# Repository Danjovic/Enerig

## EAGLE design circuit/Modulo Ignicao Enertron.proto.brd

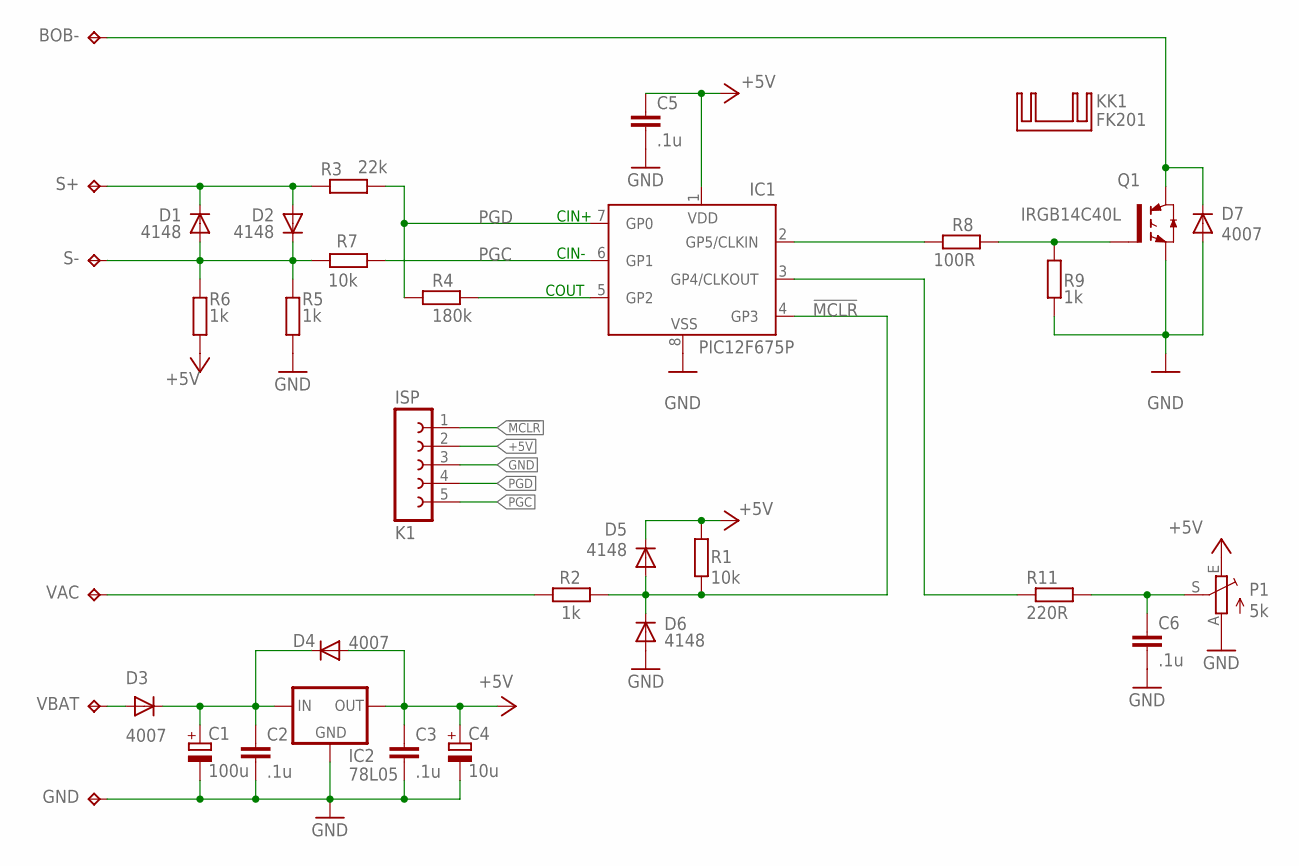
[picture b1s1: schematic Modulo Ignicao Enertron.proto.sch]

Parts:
BOB-: TPPAD1-13Y; P1-13Y
C1: 100u; E2,5-6
C2, C3, C5, C6: .1u; C050-025X075L
C4: 10u; E2-4
D1, D2, D5, D6: 4148; D-5L
D3, D4: 4007; D-7.5
D7: 4007; DO07
GND: TPPAD1-13Y; P1-13Y
IC1: PIC12F675P; DIL8
IC2: 78L05; TO92-
K1: ISP; FE05-1
KK1: FK201
P1: 5k; CA6V
Q1: IRGB14C40L; TO262-V
R1, R7: 10k; 0207/7L
R2, R5, R6, R9: 1k; 0207/7L
R3: 22k; 0207/7L
R4: 180k; 0207/7L
R8: 100R; 0207/7L
R11: 220R; 0207/7L
S+: TPPAD1-13Y; P1-13Y
S-: TPPAD1-13Y; P1-13Y
VAC: TPPAD1-13Y; P1-13Y
VBAT: TPPAD1-13Y; P1-13Y

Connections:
!MCLR: D5.A, D6.C, IC1.4 (GP3), K1.1, R1.3 (1), R2.3 (1)
+5V: C3.1, C4.+, C5.1, D4.A, D5.C, IC1.1 (VDD), IC2.3 (OUT), K1.2, P1.E, R1.4 (2), R6.3 (1)
COUT: IC1.5 (GP2), R4.4 (2)
GND: C1.-, C2.2, C3.2, C4.-, C5.2, C6.2, D6.A, D7.A, GND.TP, IC1.8 (VSS), IC2.2 (GND), K1.3, P1.A, Q1.3 (E), R5.3 (1), R9.3 (1)
unnamed: C1.+, C2.1, D3.C, D4.C, IC2.1 (IN)
unnamed: D1.A, D2.C, R5.4 (2), R6.4 (2), R7.4 (2), S-.TP
unnamed: IC1.2 (GP5/CLKIN), R8.3 (1)
unnamed: D1.C, D2.A, R3.3 (1), S+.TP
unnamed: Q1.1 (G), R8.4 (2), R9.4 (2)
unnamed: D3.A, VBAT.TP
unnamed: IC1.3 (GP4/CLKOUT), R11.3 (1)
unnamed: C6.1, P1.S, R11.4 (2)
unnamed: BOB-.TP, D7.C, Q1.2 (C)
unnamed: R2.4 (2), VAC.TP
PGC: IC1.6 (GP1), K1.5, R7.3 (1)
PGD: IC1.7 (GP0), K1.4, R3.4 (2), R4.3 (1)

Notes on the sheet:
CIN+
CIN-
COUT

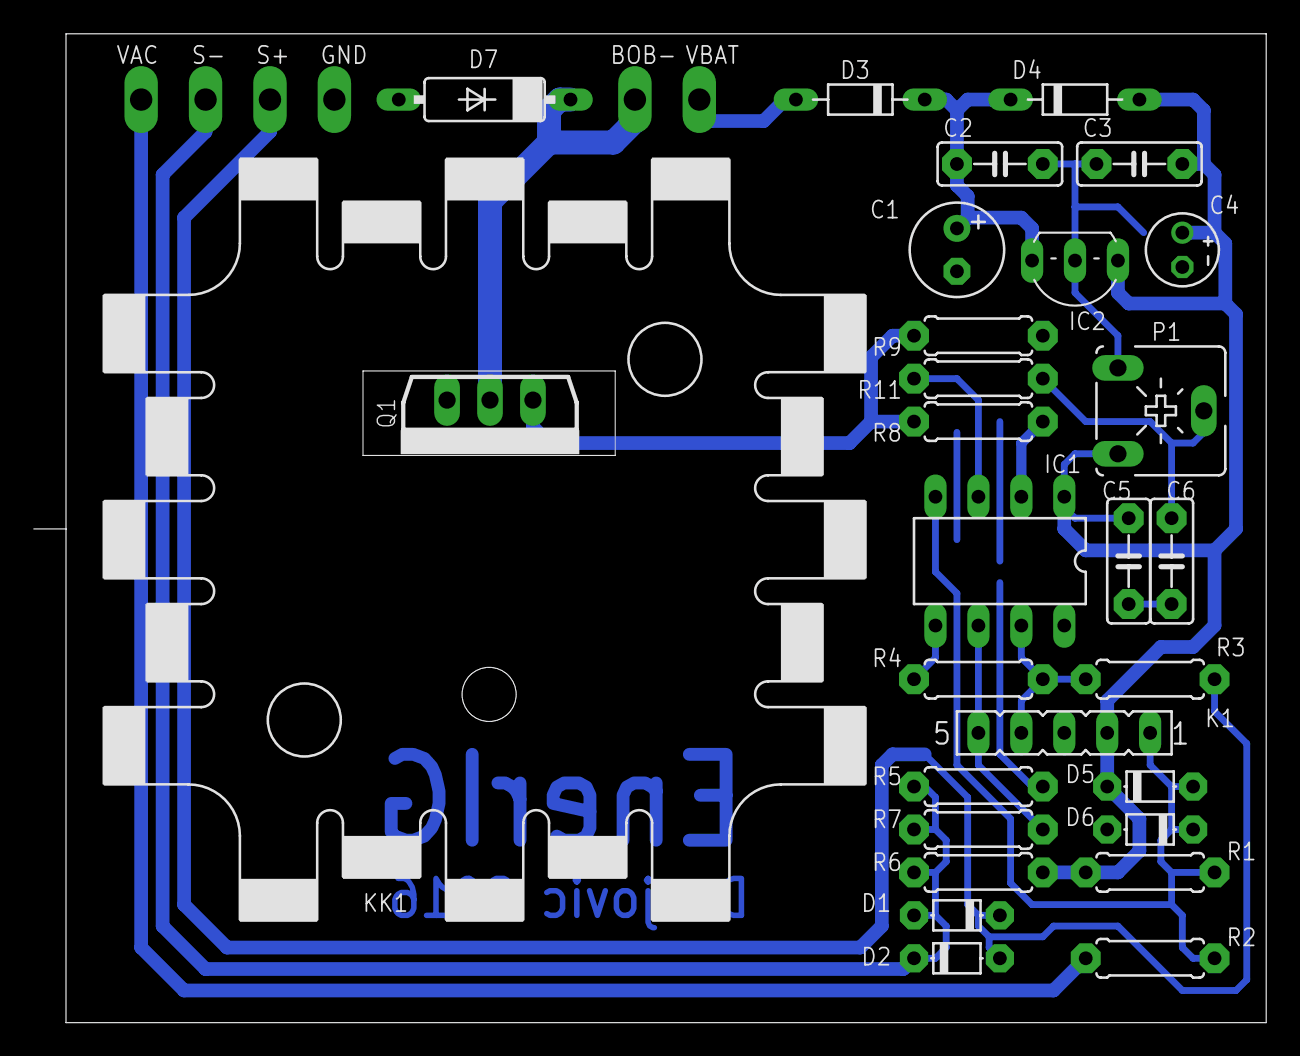
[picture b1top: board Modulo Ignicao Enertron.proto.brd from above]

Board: 2 copper layers, 72.9 x 58.5 mm, 35 parts (0 on the bottom side), 16 nets.

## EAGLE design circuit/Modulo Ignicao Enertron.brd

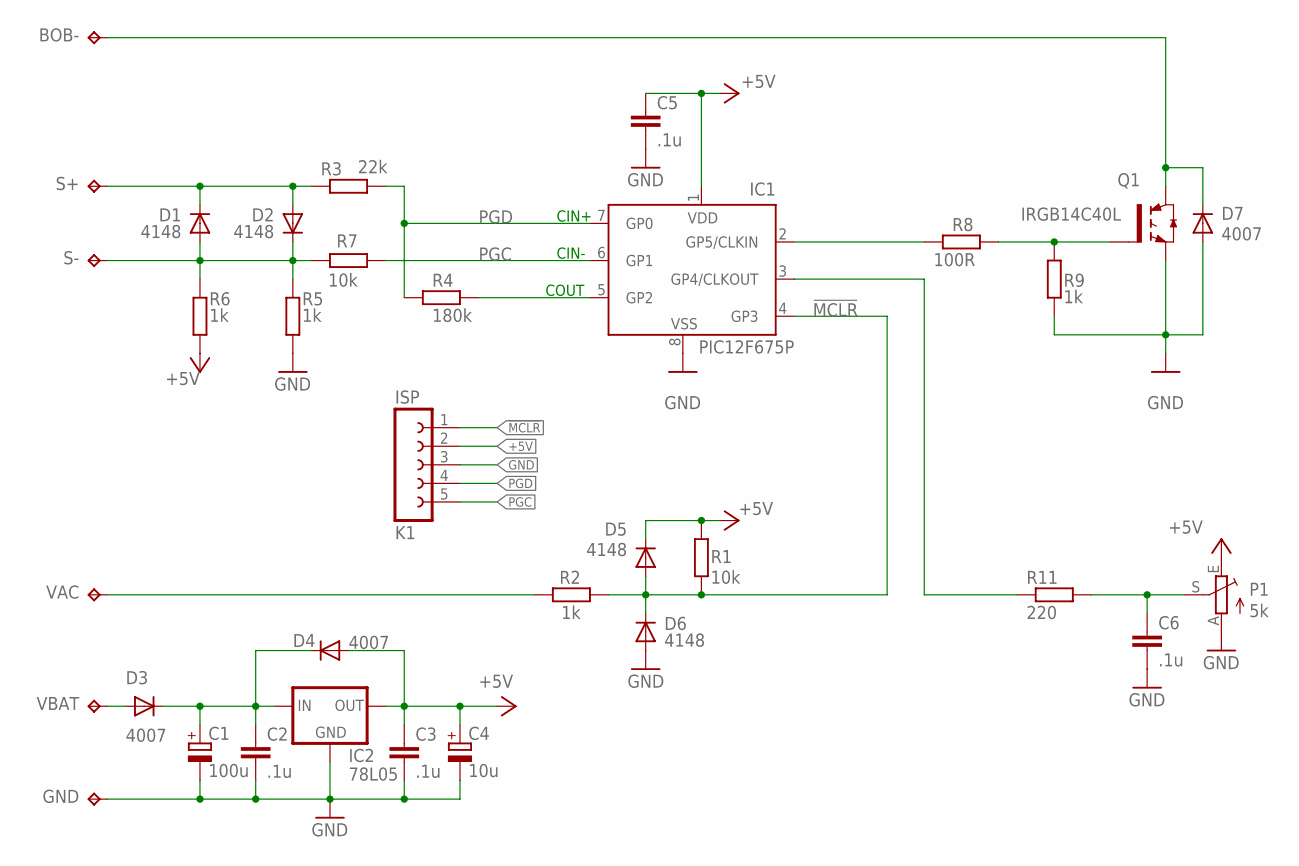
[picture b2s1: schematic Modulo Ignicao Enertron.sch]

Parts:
BOB-: TPPAD1-13Y; P1-13Y
C1: 100u; E2,5-6
C2, C3, C5, C6: .1u; C050-024X044
C4: 10u; E2-4
D1, D2, D5, D6: 4148; D-5
D3, D4, D7: 4007; D-7.5
GND: TPPAD1-13Y; P1-13Y
IC1: PIC12F675P; DIL8
IC2: 78L05; 78LXX
K1: ISP; FE05-1
P1: 5k; CA6V
Q1: IRGB14C40L; TO262-V
R1, R7: 10k; 0204/7
R2, R5, R6, R9: 1k; 0204/7
R3: 22k; 0204/7
R4: 180k; 0204/7
R8: 100R; 0204/7
R11: 220; 0204/7
S+: TPPAD1-13Y; P1-13Y
S-: TPPAD1-13Y; P1-13Y
VAC: TPPAD1-13Y; P1-13Y
VBAT: TPPAD1-13Y; P1-13Y

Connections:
!MCLR: D5.A, D6.C, IC1.4 (GP3), K1.1, R1.1, R2.1
+5V: C3.1, C4.+, C5.1, D4.A, D5.C, IC1.1 (VDD), IC2.OUT, K1.2, P1.E, R1.2, R6.1
COUT: IC1.5 (GP2), R4.2
GND: C1.-, C2.2, C3.2, C4.-, C5.2, C6.2, D6.A, D7.A, GND.TP, IC1.8 (VSS), IC2.GND, K1.3, P1.A, Q1.3 (E), R5.1, R9.1
unnamed: C1.+, C2.1, D3.C, D4.C, IC2.IN
unnamed: D1.A, D2.C, R5.2, R6.2, R7.2, S-.TP
unnamed: IC1.2 (GP5/CLKIN), R8.1
unnamed: D1.C, D2.A, R3.1, S+.TP
unnamed: Q1.1 (G), R8.2, R9.2
unnamed: D3.A, VBAT.TP
unnamed: IC1.3 (GP4/CLKOUT), R11.1
unnamed: C6.1, P1.S, R11.2
unnamed: BOB-.TP, D7.C, Q1.2 (C)
unnamed: R2.2, VAC.TP
PGC: IC1.6 (GP1), K1.5, R7.1
PGD: IC1.7 (GP0), K1.4, R3.2, R4.1

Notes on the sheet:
CIN+
CIN-
COUT

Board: 2 copper layers, 34 parts (0 on the bottom side), 16 nets, no tracks yet.

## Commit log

2016-05-03 :boom::camel: Added .gitattributes & .gitignore files
2016-05-14 Basic Release
    Basic release for Ignition controller for Enertron engine
2016-05-17 Corrected circuit around MCLR
    Corrected circuit around MCLR pin to allow ICSP. The diode network was
    bypassing MCLR high voltage to VCC. A series resistor fixed the problem.
2016-06-14 Added dwell control - variable/legacy mode
